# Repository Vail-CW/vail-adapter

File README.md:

# Vail Adapter: Morse Code Key / Paddle to USB

<p align="center">
  
  &nbsp;&nbsp;
  
</p>

The Vail Adapter is a small USB gadget that turns your Morse key or paddle into a USB device. It shows up as both a keyboard and a MIDI device, so it works with [Vail](https://vail.woozle.org/), [VBand](https://hamradio.solutions/vband/), and pretty much any CW software. The keyer logic and the sidetone run on the adapter itself, so there is no browser or operating system latency in your keying, even when you are running fast. It works on SAMD21 boards (the Seeed XIAO, the Adafruit QT Py, and the TRRS Trinkey), and there is an experimental build for the AVR Arduino Micro.

Here is a short video that shows what it can do: [Vail Adapter benefits](https://www.youtube.com/watch?v=XQ-mwdyLkOY) (4:46).

## What it does

* With Vail you can keep keying even when the Vail window is not focused, because Vail uses MIDI and MIDI does not care which window has focus
* Keyboard based apps like VBand work too, but their window has to stay focused, since keyboard presses only reach the window that is focused
* Runs all nine Vail keyer modes on the adapter, so you can key as fast as you want with no latency
* Has an optional sidetone generator, which helps with latency and lets you turn off your computer speaker
* Plays the received signal on the adapter so you can keep the computer quiet
* Stores CW memories: three slots, about 25 seconds each on SAMD21, and about 12 seconds each on the Arduino Micro
* Can key a radio directly through the optional radio output on the Advanced PCB
* Can be set up over MIDI for speed, tone, keyer type, paddle swap, and mode (see [MIDI integration](#midi-integration))
* Can swap dit and dah over MIDI, for everything or just the touch pads
* Has a passthrough mode, so an app can get the raw dit and dah paddles over MIDI and do its own keying
* Has a Keyboard Sim mode that decodes your Morse and types it like a keyboard. Key KSKS as its own word to turn it on, and unplug to turn it off
* Gets free firmware updates for life

## Where to get one

If you would rather not build your own, I sell them at [shop.ke9bos.com](https://shop.ke9bos.com). You can get a bare PCB, a full kit with everything you need, or a finished unit that is ready to plug in.

If you want to special order parts, place a bulk order, or you have a question about anything Vail related, email me at ke9bos@pigletradio.org and I will take care of you.

## Updating the firmware

You can flash the latest firmware right from your browser (Chrome, Edge, or Opera) at [update.vailadapter.com](https://update.vailadapter.com). Choose your board, pick a version, and follow the steps on the page. Every firmware version is posted on the [releases page](https://github.com/Vail-CW/vail-adapter/releases).

## First time setup

Once you have flashed an adapter, the first thing to do is run the getting started tool at [vailadapter.com/gettingstarted](https://vailadapter.com/gettingstarted). It walks you through getting set up and making sure everything is working.

The full manual is on the website at [vailadapter.com/manual](https://vailadapter.com/manual). It covers the buttons, the keyer modes, the memories, and the rest of the day to day use.

## Building your own

Step by step assembly guides for both boards are on the website at [vailadapter.com/assembly](https://vailadapter.com/assembly), and the PDFs are kept in this repo too: [Basic PCB v2](online-updater/assembly/BasicPCBV2.pdf) and [Advanced](online-updater/assembly/AdvancedAdapterAssemblyInstructions.pdf). If you would rather not source parts and solder, you can get a kit or a finished unit from [shop.ke9bos.com](https://shop.ke9bos.com).

The board designs (KiCad and gerbers) and the printable cases are in [hardware/](hardware/), organized by variant.

### Basic PCB (v2)

* Seeed Studio XIAO SAMD21 (from [Amazon](https://www.amazon.com/gp/product/B08CN5YSQF?smid=A2OY3Y9CEYQQ5W)) or an [Adafruit QT Py SAMD21](https://www.adafruit.com/product/4600)
* A buzzer speaker
* A [PCB mount TRS connector](https://a.co/d/bLaRwym)
* A [switched PCB mount aux jack](https://www.amazon.com/dp/B07WR748JS)

You can order the bare PCB from JLCPCB or PCBWAY yourself, or get a bare board, a kit, or an assembled unit from [shop.ke9bos.com](https://shop.ke9bos.com).

### Advanced PCB

The Advanced PCB does everything the Basic does and adds a radio output, so you can key a rig directly, along with capacitive touch points. It uses more parts than the Basic build:

* Seeed Studio XIAO SAMD21 or an Adafruit QT Py SAMD21
* A buzzer speaker
* The Advanced Vail Adapter PCB
* 1 switching aux jack and 2 standard aux jacks
* 2 transistors and 2 resistors, which drive the radio output
* 2 screw terminal PCB mounts
* 2 headers for the Arduino

The radio output parts are easy to get wrong when you buy them one at a time, so most people get the Advanced build as a kit or assembled from [shop.ke9bos.com](https://shop.ke9bos.com). The full build steps are in the [Advanced assembly guide](online-updater/assembly/AdvancedAdapterAssemblyInstructions.pdf).

### Without a PCB

* Seeed Studio XIAO SAMD21 (or an Adafruit QT Py SAMD21)
* A buzzer speaker
* A [panel mount aux jack](https://www.amazon.com/dp/B01C3RFHDC)

### Vail Lite, the USB stick version

* An [Adafruit TRRS Trinkey M0](https://www.adafruit.com/product/5954), which is a USB stick sized board with a TRRS jack built in
* A piezo buzzer, connected through the STEMMA QT connector
* It has no buttons, no capacitive touch, no headphone jack, and no radio output, so you change settings over MIDI
* Full instructions are in [TRRS_TRINKEY_BUILD.md](docs/TRRS_TRINKEY_BUILD.md)

### Arduino Micro (experimental)

This is a 5V AVR alternative to the SAMD21 boards. It is for DIY and breadboard builds only, and there is no PCB made for it.

* Wiring: D2 is Dit, D1 is Dah, D0 is the Straight Key, D10 is the Piezo, and GND is ground. There is a full walkthrough in [docs/advanced-install.md](docs/advanced-install.md).
* A few things it cannot do compared to the SAMD21 boards: no capacitive touch, no button menu, and no status LEDs. The CW memories are shorter at about 12 seconds each, and the radio output on A2 and A3 runs at 5V, so check that your radio can handle it or use a level shifter.
* Flashing is different too. It uses WebSerial with the AVR109 (Caterina) bootloader instead of UF2 drag and drop. Flash it at [update.vailadapter.com](https://update.vailadapter.com) by choosing DIY No PCB and then Arduino Micro in Chrome, Edge, or Opera, or run `arduino-cli upload --fqbn arduino:avr:micro`.

## Setting it up

* [Easy Setup](docs/easy-install.md)
* [Advanced Setup](docs/advanced-install.md)
* [See some that other people have built](https://github.com/Vail-CW/vail-adapter/wiki#cool-people-who-have-built-one)

The full manual is at [vailadapter.com/manual](https://vailadapter.com/manual).

## MIDI integration

The adapter is a standard USB MIDI device. Software can set the mode, the speed, the sidetone, and the keyer type, and it can read the keyed output as MIDI notes. The whole protocol, including the message types, the value ranges, and exactly how the firmware responds, is written up in [MIDI_INTEGRATION_SPEC.md](docs/MIDI_INTEGRATION_SPEC.md). If you are building something that talks to the adapter, follow that document closely, because I keep the existing MIDI commands the same on purpose. There is more about that just below.

## Contributing

I am glad to have help with this project. If you have a question, want parts, or want to talk through an idea, email me at ke9bos@pigletradio.org. If the adapter has been useful to you and you want to support more work on it, you can [buy me a coffee](https://buymeacoffee.com/ke9bos).

### Guidelines

The Vail Adapter has one job and it does it well. It is a simple, reliable, low latency bridge from a Morse key or paddle to USB. A lot of people, and a lot of outside tools, already count on the way it works today, so I review changes with that in mind. Here is what I ask:

1. Do not change the existing MIDI commands. The MIDI commands that are already there, for mode, speed, tone, keyer selection, and the dit, dah, and straight key notes the adapter sends, are something other tools and the Vail and VBand sites depend on. The commands, the value ranges, and the note numbers need to stay exactly as they are. I am happy to look at new MIDI commands, as long as they use messages that are not already being used and they do not change or interfere with anything that already works. If you add one, update the MIDI spec to match.

2. Keep it backward compatible. Do not break the things people already rely on, like the keyboard output (Dit is Left Control and Dah is Right Control), starting up in keyboard mode, saved settings, or the USB keyboard and MIDI interfaces. If you change how settings are stored, make sure the settings people already have still load.

3. Keep it fast. The reason this thing exists is lag free keying. Do not add anything that slows down the path from the paddle to the output. If a feature needs heavy work, do that work somewhere other than the keying loop.

4. Keep it focused. This is a key and paddle adapter. It does keying, keyer modes, sidetone, CW memories, and the optional radio output. Bigger ideas like a display, WiFi, logging, or training games belong on the Vail Summit, not here.

5. Add new hardware without disturbing the old. If you add support for a new board, put it behind a setting in config.h so the boards that already work keep behaving exactly the same. The Arduino Micro support is a good example of this.

6. Make sure every board still builds. A change should not fix one board by breaking another. Check that all of the configurations still compile before you send it.

7. Watch the limits of the chips. There is not a lot of room to spare, especially on the Arduino Micro. New features have to fit without using up the headroom on the boards that already work.

8. Do not change the defaults without a good reason. The default keyer, speed, tone, and startup mode are what people expect when they turn it on. Changing them catches people off guard.

9. Add to it rather than change it. When you can, add a new mode, command, or setting instead of changing how an existing one behaves.

10. Talk to me before any big change. For a large rewrite or a whole new feature, open an issue or send me an email first so we can make sure it fits where the project is going.

## License and credits

* License: MIT. See [LICENSE.md](LICENSE.md).
* Originally written by Neale Pickett. Currently maintained by Brett Hollifield, KE9BOS.
* Contact: ke9bos@pigletradio.org

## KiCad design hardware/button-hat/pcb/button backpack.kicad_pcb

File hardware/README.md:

# Hardware

Board designs and printable cases for the Vail Adapter, organized by variant.
Each variant folder holds the PCB design and, where there is one, the matching
3D printable case.

- `basic-adapter/`
  - `pcb/` - KiCad project and gerbers for the Basic PCB
  - `case/` - printable case (STL) and Fusion 360 source (.f3d)
- `advanced-adapter/`
  - `pcb/` - KiCad project and gerbers for the Advanced PCB (adds radio output)
  - `case/` - printable case and Fusion 360 source
- `button-hat/`
  - `pcb/` - KiCad project and gerbers for the button hat add on

Order bare PCBs from JLCPCB or PCBWAY using the gerber zip in each `pcb/` folder,
or get a kit or a finished unit from [shop.ke9bos.com](https://shop.ke9bos.com).
Step by step assembly guides are at [vailadapter.com/assembly](https://vailadapter.com/assembly).

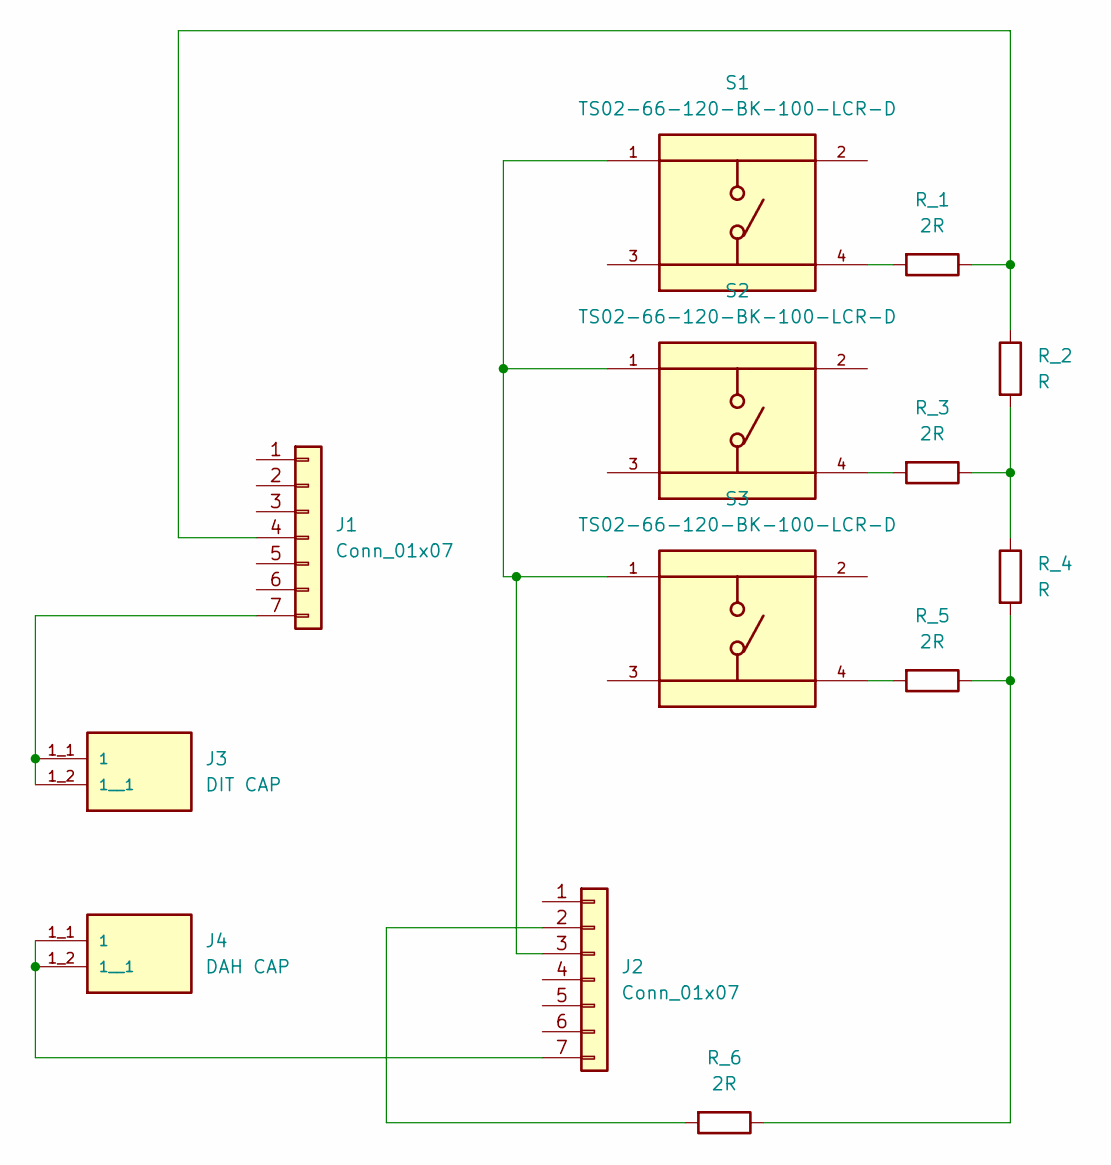
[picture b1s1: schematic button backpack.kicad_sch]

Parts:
J1, J2: Conn_01x07; PinHeader_1x07_P2.54mm_Vertical
J3: DIT CAP; KEYSTONE_7837; PARTREV 3.14.19
J4: DAH CAP; KEYSTONE_7837; PARTREV 3.14.19
R_1, R_3, R_5, R_6: 2R; R_Axial_DIN0207_L6.3mm_D2.5mm_P10.16mm_Horizontal
R_2, R_4: R; R_Axial_DIN0207_L6.3mm_D2.5mm_P10.16mm_Horizontal
S1, S2, S3: TS02-66-120-BK-100-LCR-D; SW_TS02-66-120-BK-100-LCR-D; PARTREV 1.0

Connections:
unnamed: J1.4, R_1.1, R_2.1
unnamed: J1.7, J3.1_1 (1), J3.1_2 (1__1)
unnamed: J2.2, R_6.2
unnamed: J2.3, S1.1, S2.1, S3.1
unnamed: J2.7, J4.1_1 (1), J4.1_2 (1__1)
unnamed: R_1.2, S1.4
unnamed: R_2.2, R_3.1, R_4.1
unnamed: R_3.2, S2.4
unnamed: R_4.2, R_5.1, R_6.1
unnamed: R_5.2, S3.4

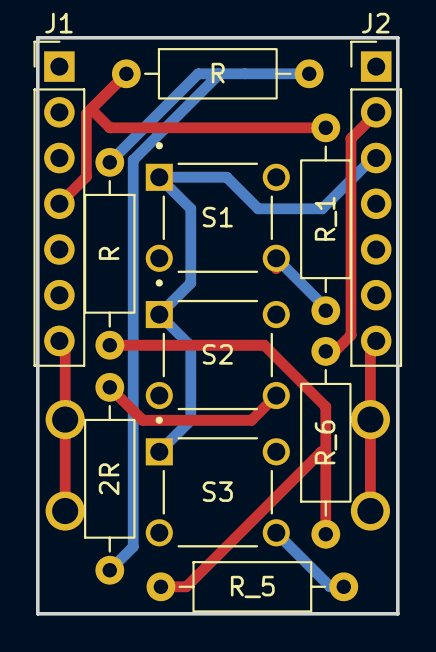
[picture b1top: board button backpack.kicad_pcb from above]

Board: 2 copper layers, 20.0 x 32.0 mm, 13 parts (0 on the bottom side), 10 nets.

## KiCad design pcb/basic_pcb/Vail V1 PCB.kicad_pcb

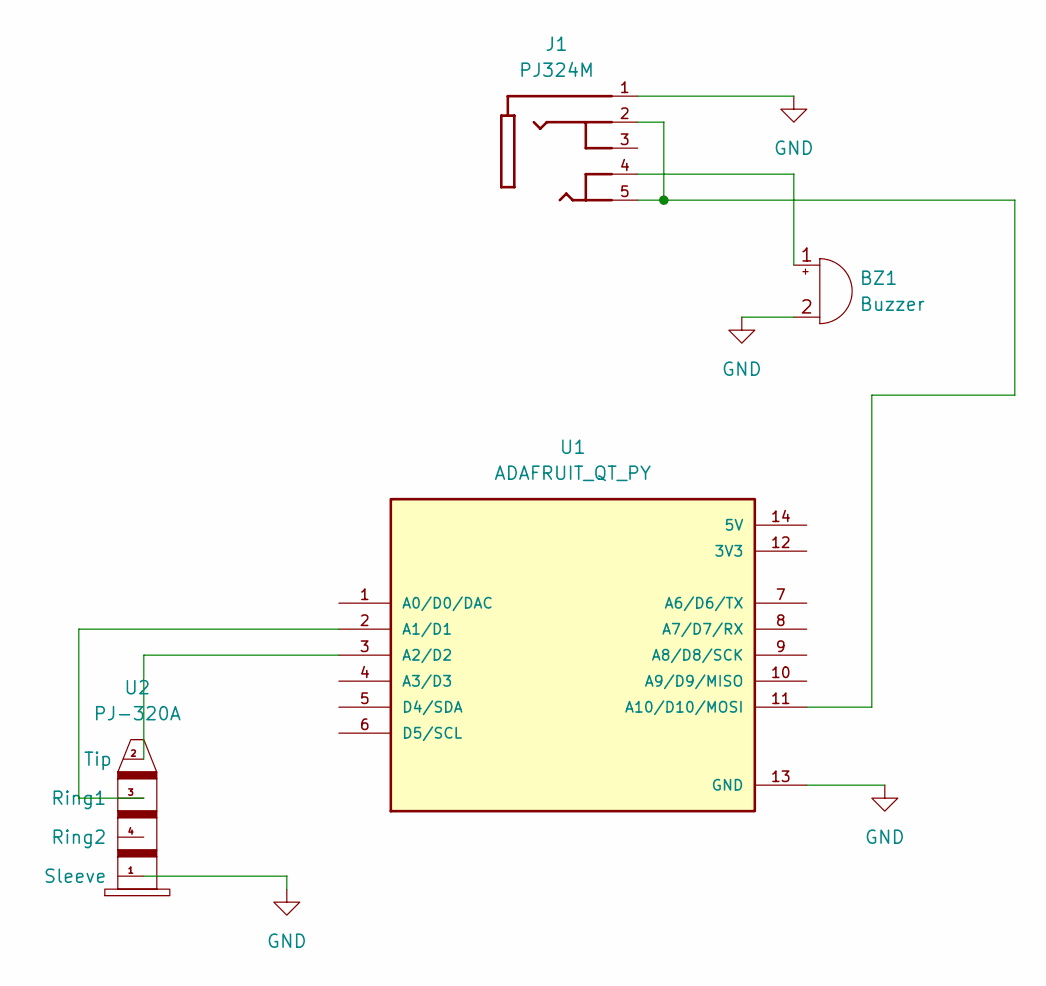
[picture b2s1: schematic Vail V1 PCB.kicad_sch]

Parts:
BZ1: Buzzer; Buzzer_15x7.5RM7.6
J1: PJ324M; WENZHOU_PJ324M; PARTREV N/A
U1: ADAFRUIT_QT_PY; MODULE_ADAFRUIT_QT_PY; PARTREV 2022-12-12
U2: PJ-320A; TRRS-PJ-320A

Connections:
GND: BZ1.2 (-), J1.1, U1.13 (GND), U2.1 (Sleeve)
unnamed: BZ1.1 (+), J1.4
unnamed: U1.2 (A1/D1), U2.3 (Ring1)
unnamed: U1.3 (A2/D2), U2.2 (Tip)
unnamed: J1.2, J1.5, U1.11 (A10/D10/MOSI)

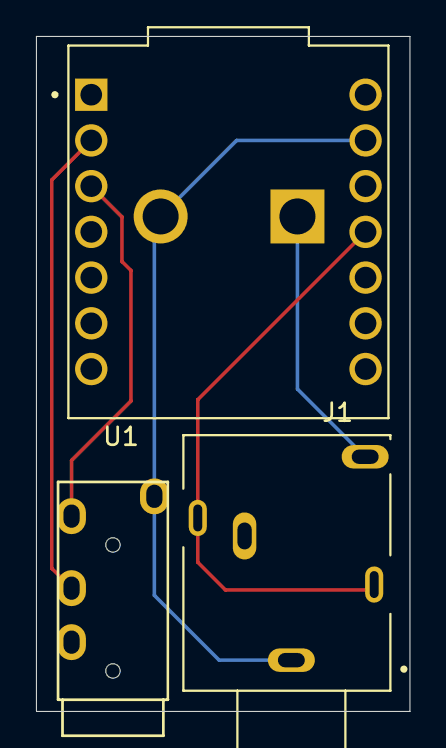
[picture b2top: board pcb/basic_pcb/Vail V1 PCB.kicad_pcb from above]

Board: 2 copper layers, 20.8 x 37.5 mm, 4 parts (1 on the bottom side), 5 nets.

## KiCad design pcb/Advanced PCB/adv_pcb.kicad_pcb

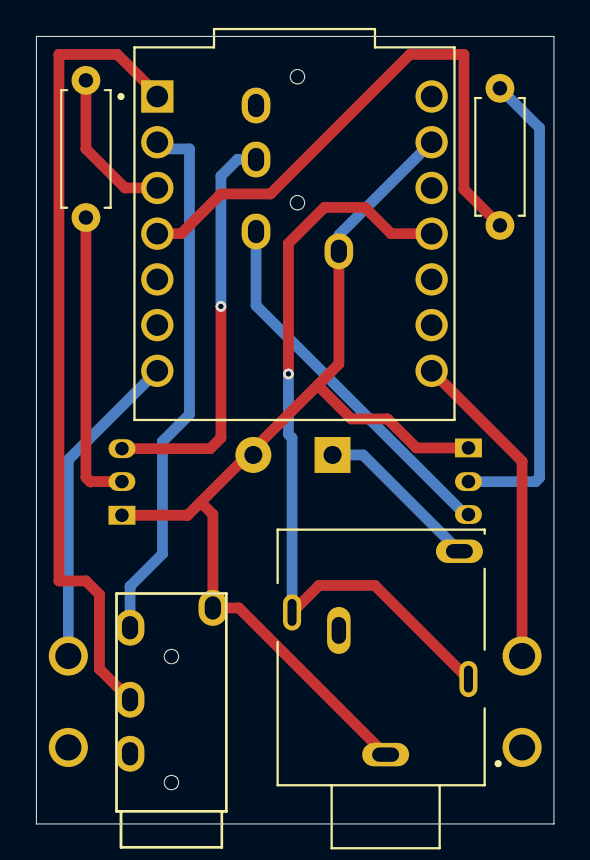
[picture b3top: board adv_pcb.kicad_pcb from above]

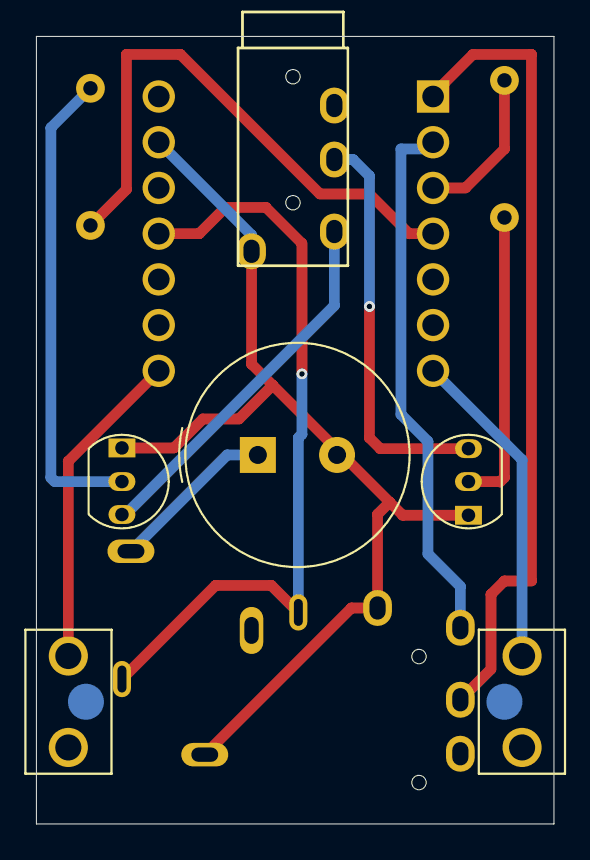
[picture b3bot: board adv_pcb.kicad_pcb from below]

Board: 2 copper layers, 28.8 x 43.8 mm, 13 parts (8 on the bottom side), 13 nets.

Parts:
BZ1: Buzzer; Buzzer_TDK_PS1240P02BT_D12.2mm_H6.5mm
DAH2: PN2222A; TO-92_Inline
DIT2: PN2222A; TO-92_Inline
Dah1: 7837; KEYSTONE_7837
Dit1: 7837; KEYSTONE_7837
J1: headphone; WENZHOU_PJ324M
R1, R2: R; R_Axial_DIN0207_L6.3mm_D2.5mm_P7.62mm_Horizontal
TP1, TP2: TestPoint; TestPoint_Pad_D4.0mm
U1: ADAFRUIT_QT_PY; MODULE_ADAFRUIT_QT_PY
U2: Output to Radio; TRRS-PJ-320A
U3: Key Input; TRRS-PJ-320A

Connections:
GND: BZ1.2 (-), DAH2.1 (E), DIT2.1 (E), J1.1, U1.13 (GND), U2.1 (Sleeve), U3.1 (Sleeve)
unnamed: BZ1.1 (+), J1.4
unnamed: DAH2.2 (B), R1.1
unnamed: DAH2.3 (C), U2.3 (Ring1)
unnamed: DIT2.2 (B), R2.1
unnamed: DIT2.3 (C), U2.2 (Tip)
unnamed: Dah1.1_2 (1__1), U1.8 (A7/D7/RX)
unnamed: Dit1.1_1 (1), U1.7 (A6/D6/TX)
unnamed: U1.1 (A0/D0/DAC), U3.3 (Ring1)
unnamed: U1.2 (A1/D1), U3.2 (Tip)
unnamed: R1.2, U1.3 (A2/D2)
unnamed: R2.2, U1.4 (A3/D3)
unnamed: J1.2, J1.5, U1.11 (A10/D10/MOSI)

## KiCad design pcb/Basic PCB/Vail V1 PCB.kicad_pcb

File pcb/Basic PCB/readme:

This is where we have the basic PCB files. This would be what most folks likely have if you have built one off of a pcb in 2025 or bought a PCB or kit from Brett KE9BOS. 

This version is the most recent version(v1.1 as of 4/19/2025), and includes the second aux jack for headphones. When you plug in headphones, the buzzer auto mutes. 

If you have a pcb only one aux jack(v1), that one will continue to be supported with the code in this project but was replaced with the new pcb design. Same functionality besides the output jack for the headphones. 

Black PCB = v1 basic

Purple PCB = v1.1 basic

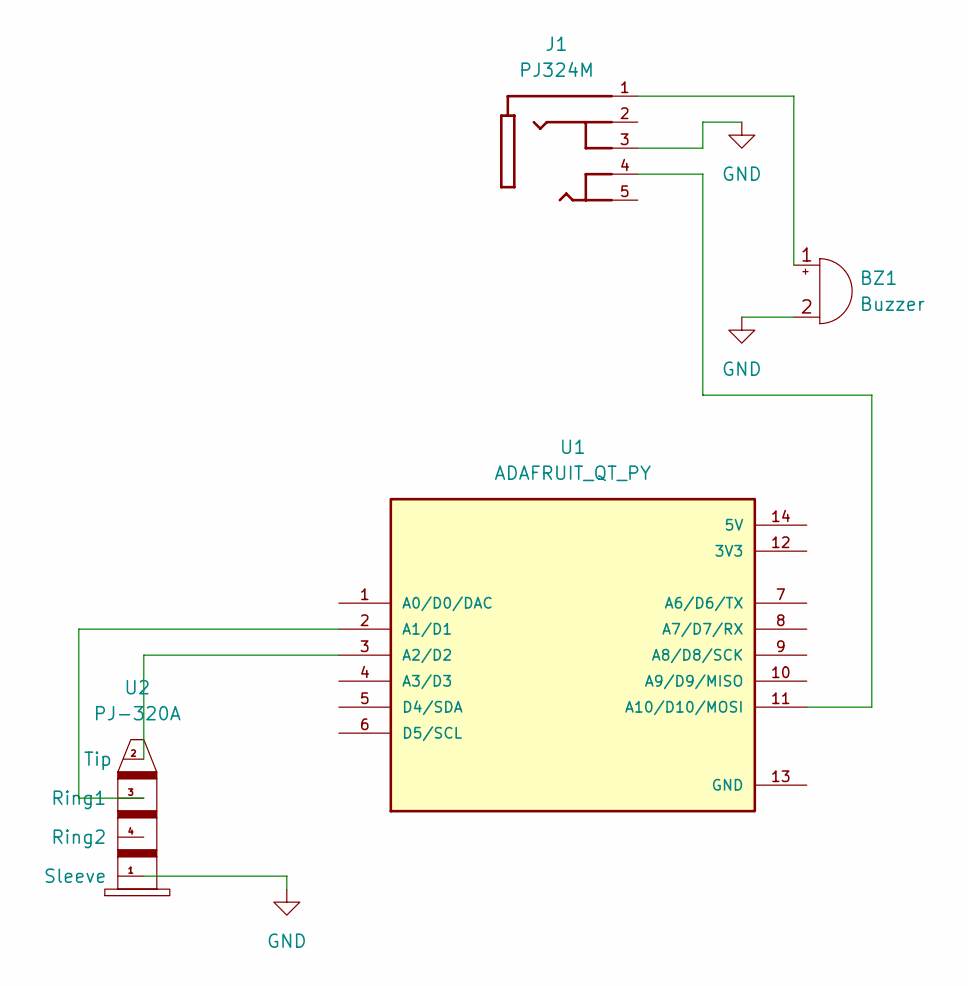
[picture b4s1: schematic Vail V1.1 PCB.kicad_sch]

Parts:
BZ1: Buzzer; Buzzer_15x7.5RM7.6
J1: PJ324M; WENZHOU_PJ324M; PARTREV N/A
U1: ADAFRUIT_QT_PY; MODULE_ADAFRUIT_QT_PY; PARTREV 2022-12-12
U2: PJ-320A; TRRS-PJ-320A

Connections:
GND: BZ1.2 (-), J1.3, U2.1 (Sleeve)
unnamed: BZ1.1 (+), J1.1
unnamed: U1.2 (A1/D1), U2.3 (Ring1)
unnamed: U1.3 (A2/D2), U2.2 (Tip)
unnamed: J1.4, U1.11 (A10/D10/MOSI)

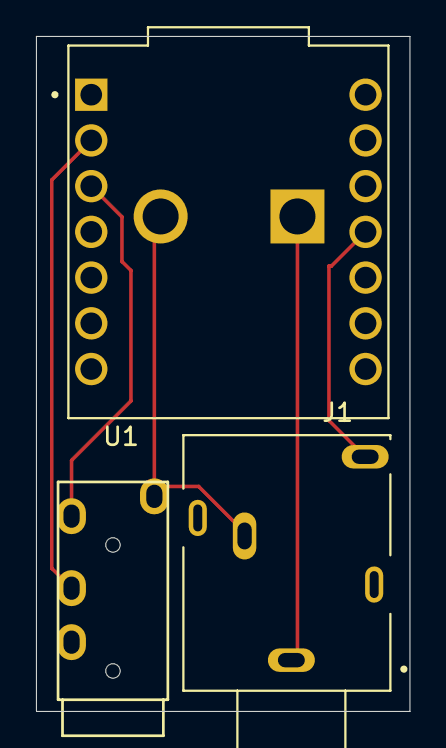
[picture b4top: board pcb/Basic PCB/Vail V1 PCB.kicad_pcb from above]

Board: 2 copper layers, 20.8 x 37.5 mm, 4 parts (1 on the bottom side), 5 nets.

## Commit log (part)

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2025-06-06 Create Basic_PCB
2025-06-23 Update adapter.h
    multi keybd key send update
2025-08-04 Update easy-install.md
    Reference discord
2025-08-04 Corrected a spelling mistake: 'macth' → 'match'
2025-08-18 Update adapter.h, revert for radio mode issue
2025-09-01 Rename PCB lid STL file for clarity
2025-09-09 Add adv case lid STL file
2025-09-09 Rename vail v2 gerber.zip to adv_pcb gerber.zip
2025-10-02 Update firmware UF2 files
2025-10-04 Removed marked down file replaced with a pdf
2025-10-16 example code for buttons
2025-10-27 Update CLAUDE.md with correct repository context for vail-summit branch
2025-10-27 Remove .gitignore from vail-summit branch
2025-10-30 Update Summit firmware from vail-summit branch [skip ci]
    Built from branch: vail-summit
    Commit: 5a2b4f023a26cfd54b9c73aa51758b82fb1c1301
    Firmware files:
    - bootloader.bin
    - partitions.bin
    - vail-summit.bin
2025-10-30 Update Summit firmware from vail-summit branch [skip ci]
    Built from branch: vail-summit
    Commit: 671f486da9b904b32ef0467433482707496f8df0
    Firmware files:
    - bootloader.bin
    - partitions.bin
    - vail-summit.bin
2025-10-30 Update Summit firmware from vail-summit branch [skip ci]
    Built from branch: vail-summit
    Commit: 870e1b5af5bdd0a688ea2afbcf01f20706286bd9
    Firmware files:
    - bootloader.bin
    - partitions.bin
    - vail-summit.bin
2025-11-03 Remove .claude directory from tracking
2025-11-07 Update Summit firmware from vail-summit branch [skip ci]
    Built from branch: vail-summit
    Commit: 29d6577f502d7cbeeb54e4cf4311d6b89d78de12
    Firmware files:
    - bootloader.bin
    - partitions.bin
    - vail-summit.bin
2025-11-10 Update Summit firmware from vail-summit branch [skip ci]
    Built from branch: vail-summit
    Commit: e7f2c2c3749a56db28f8144a54d6010690d7919a
    Firmware files:
    - bootloader.bin
    - partitions.bin
    - vail-summit.bin
2025-11-10 Update Summit firmware from vail-summit branch [skip ci]
    Built from branch: vail-summit
    Commit: 2f090397cd0e4a90509a2588b5d2abec52bcc2ba
    Firmware files:
    - bootloader.bin
    - partitions.bin
    - vail-summit.bin
2025-11-11 Update Summit firmware from vail-summit branch [skip ci]
    Built from branch: vail-summit
    Commit: 27ef8636c6a7e69f9000805119f76b590edb33cb
    Firmware files:
    - bootloader.bin
    - partitions.bin
    - vail-summit.bin
2025-12-28 Add NimBLE-Arduino library to build workflow
2025-12-29 Update Summit firmware from vail-summit branch [skip ci]
    Built from branch: vail-summit
    Commit: daa949000fd36dac98c64ae20966ed02d4cd2065
    Firmware files:
    - bootloader.bin
    - partitions.bin
    - vail-summit.bin
2025-12-30 Update Summit firmware from vail-summit branch [skip ci]
    Built from branch: vail-summit
    Commit: c1e0200a00f6a043072bccf2548492098121ff0a
    Firmware files:
    - bootloader.bin
    - partitions.bin
    - vail-summit.bin
2025-12-31 Update Summit firmware from vail-summit branch [skip ci]
    Built from branch: vail-summit
    Commit: d2b5449809a1f4efed119b342c097769a1443b0b
    Firmware files:
    - bootloader.bin
    - partitions.bin
    - vail-summit.bin
2025-12-31 Update Summit firmware from vail-summit branch [skip ci]
    Built from branch: vail-summit
    Commit: 06ca5ee54ef44e5db0f1e493105009db9fafcc54
    Firmware files:
    - bootloader.bin
    - partitions.bin
    - vail-summit.bin
2026-01-04 Update Summit firmware from vail-summit branch [skip ci]
    Built from branch: vail-summit
    Commit: 0dd58916b27ada8817c34e689a111ed3267439a2
    Firmware files:
    - bootloader.bin
    - partitions.bin
    - vail-summit.bin
2026-01-18 Update Summit firmware from vail-summit branch [skip ci]
    Built from branch: vail-summit
    Commit: f382073184d14d8cdafcf709fb631d3c054dfb7a
    Firmware files:
    - bootloader.bin
    - partitions.bin
    - vail-summit.bin
2026-03-21 Upload files for 3D Printed Cases with Buttons
2026-04-22 Update firmware files (UF2 + HEX)
2026-05-10 summit firmware workflow: place lv_conf.h next to lvgl library
    LVGL's lv_conf_internal.h does '#include "../../lv_conf.h"' relative
    to its src/misc/ folder, expecting the config one directory above the
    lvgl/ library. Local Vail Summit builds satisfy this by keeping a copy
    of lv_conf.h in arduino-cli/user/libraries/ alongside the lvgl folder.
    CI installs lvgl into ~/Arduino/libraries/lvgl/ but doesn't have a
    matching lv_conf.h next to it, so the build was failing with:
2026-05-10 summit firmware workflow: stash build outputs in /tmp before deploy checkout
    PR #72's clean: false on the second actions/checkout@v4 didn't
    prevent the vail-summit/build/ artifacts from disappearing. Even
    with clean: false set, the action seems to be wiping or reorganizing
    GITHUB_WORKSPACE in a way that loses the prior build outputs.
    Rather than wrestling with checkout's workspace handling, copy the
    three .bin files to /tmp/summit-build/ before the deploy checkout
2026-05-10 summit firmware workflow: fix binary rename (was producing 'bin' not 'vail-summit.bin') (#74)
    The Normalize step's for-loop used shell parameter expansion to strip
    the 'vail-summit.ino.' prefix:
    for f in ...; do
    mv "$f" "${f#vail-summit.ino.}"
    done
    That works for the bootloader and partitions files (e.g.
2026-05-10 summit firmware workflow: BUILD_INFO source_commit reflects vail-summit checkout (#75)
    Previously BUILD_INFO.txt's 'Source commit' field used ${{ github.sha }},
    which inside this workflow resolves to vail-adapter's master HEAD —
    not the vail-summit source actually built. For run #25631323663 this
    showed 'f53a920' (the workflow PR #74 merge commit on vail-adapter)
    instead of 'cf7ee56' (the actual vail-summit pr1-merge-and-fix tip
    that was built).
2026-06-09 chore: update TEST firmware from master @ ee56910134f07c82cf1fefdb545cc0b4d005e933
2026-06-11 Reorganize repo: distribute firmware via releases only
    - Remove docs/firmware_files/ (root, test/, summit/). Firmware is now
    distributed exclusively as GitHub Release assets.
    - build_uf2.yml: drop the deploy job that committed firmware into the repo
    and the deploy_target input; keep the build (compile check on push) and
    the release-asset attach job. Renamed to "Build Arduino Firmware".
    - Updater: remove the "Latest (from repository)" fallback and the
2026-06-11 docs: remove obsolete AUTOMATED_ISSUE_CREATION and SUMMIT_INTEGRATION
    Both described systems that no longer exist: the firmware_files-based
    public/private test-firmware model (test builds are now pre-releases) and
    the Vail Summit firmware living in this repo (Summit is its own repo now).
    Drop the dangling links to the removed auto-issue doc from
    RELEASE_TESTING_PROCESS.md.
2026-06-11 Move updater to online-updater/, make docs/ documentation only
    The GitHub Pages updater lived in docs/, which clashed with the doc/
    documentation folder. Rename so the two are clearly separated:
    - docs/ (the Pages site) -> online-updater/
    - doc/ -> docs/, and move the maintainer docs that were in the Pages folder
    (RELEASE_TESTING_PROCESS.md, TESTING_GUIDE.md, Vail Adapter Setup.pdf)
    into it, so docs/ is purely documentation.
2026-06-11 Reorganize hardware files under hardware/ by variant
    Group the PCB designs and printable cases into one hardware/ folder,
    organized by adapter variant so each board and its case sit together:
    - hardware/basic-adapter/{pcb,case}
    - hardware/advanced-adapter/{pcb,case}
    - hardware/button-hat/pcb
    Flatten the redundant button-hat directory nesting, drop the empty
2026-06-12 Add Troubleshooting Recorder to updater
    Device-agnostic serial log capture page (troubleshoot.html): user picks
    their device, baud is mapped automatically (Adapter 9600, Summit 115200),
    captures serial output to save and share for debugging. Adapter path adds
    an unplug/replug 'Capture Startup' mode that latches onto the port the
    instant it re-enumerates; Summit uses an ESP reset-over-wire restart.
2026-06-12 Refer to Discord channels by name without hashtags
2026-06-13 Use short 8.3-safe firmware filenames to fix Windows flashing
    Long release-asset names like xiao_basic_pcb_v2_v5.0.uf2 force Windows to
    write a VFAT long-filename entry onto the SAMD21 bootloader's tiny emulated
    FAT volume. On some Windows 10/11 setups the drag-to-bootloader copy hangs
    or fails partway, leaving the adapter stuck in storage mode on every plug-in.
    (Reported twice in the week after the V5.0 release-asset rollout; one tester
    worked around it by flashing from Android, which confirms the file is fine and
2026-06-13 Keep GitHub asset filename on updater downloads (#79)
    The asset names are now short and 8.3-safe (e.g. xb2_50.uf2), so there's no
    reason to rename the download to VAIL_5_0.uf2 — and the GitHub name is more
    useful: it identifies the exact board/variant/version that was flashed, which
    is a standard troubleshooting question when a user reports an issue.
    Drop the Blob/short-name download path and just download the GitHub asset
    directly, keeping its exact name.
2026-06-13 Add test-only 'erase app' button to serial flasher panel
    Lets you reproduce the 'stuck in bootloader' state on demand for testing the
    serial flasher: erases only the app region (0x2000+), so the bootloader finds
    no valid app and stays in storage mode on every plug-in. Fully recoverable —
    the bootloader is never touched. Behind the hidden #serial panel, with a
    confirm() guard.
2026-06-13 Make SAM-BA handshake robust; clearer no-response error
    First hardware test returned 'no response' from the bootloader. Harden connect():
    - assert DTR/RTS on open (some WebSerial+CDC stacks withhold RX until DTR is up)
    - retry the N/V handshake up to 5x (first post-open bytes are often dropped)
    - accept either newline order instead of an exact \n\r
    - don't hard-fail when [Arduino:XYZ] isn't advertised — warn and try anyway
    - replace the cryptic timeout with a clear 'put it in bootloader mode / pick that
2026-06-13 Redesign flash step: method chooser + clean per-method flows (#83)
    The combined flash page was overloaded (plug-in + boot + UF2 download + copy +
    finalize + a bolted-on serial panel) with no clear path for non-technical users.
    Now: device -> model -> board -> 'Set up your update' (pick version + pick
    method) -> a single, clutter-free flow for the chosen method.
    - New method chooser carries the firmware version selector (shared by both
    flows) and two cards: UF2 file (recommended, default) and Web flasher (Beta),
